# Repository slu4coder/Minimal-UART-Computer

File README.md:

# Minimal UART Computer - older version with EEPROMs

Current version: https://github.com/slu4coder/Minimal-UART-CPU-FLASH-Edition

Hi there, I built my own Computer from scratch - using nothing but TTL chips, because, well, that's what I wanted to do, I guess! I wanted
a CPU that is easy to understand, fun to build and powerful enough to allow for programming educational stuff and little games on it.
Ah, and by the way - it should be as simple as possible - sort of the "Simplest Usable Personal Computer Ever". Well, in case you're
interested, this repo aims to provide you with everything you need to follow my one-and-a-half year journey down this rabbit hole. 

WHAT YOU GET HERE:

  ● Block diagram of the CPU and overview it's instruction set

  ● KiCAD project files with detailed schematics and PCB layout

  ● Gerber files ready to be submitted at any PCB manufacturer of your choice

  ● Bill of material

  ● Images in .bin format of both the ROM and the CPU's control microcode

  ● Source code of the minimal operating system MinOS and several demos and games

  ● Cross-assembler 'asm.exe' running on Windows in order to comfortably write, assemble and upload your own software

TECHNICAL SPECIFICATION:

  ● Comparable to Altair 8800 or Apple 1

  ● Clear(est?) and simple(st? – you judge!) design for fun and education

  ● 8-bit data bus, 16-bit address bus, Von-Neumann architecture

  ● 64 instructions (conditional branching, subroutines, stack and word ops)

  ● 1,8432MHz clock with 0.25Mips (Altair 8800: 0.29Mips, Apple 1: 0.43Mips)

  ● 24kB RAM / 8kB ROM (OS, memory monitor, disassembler, tools, games)

  ● UART interface (115.2kbps) for terminal display, keyboard input and file I/O

  ● 16 control signals, 2 registers A and B, ALU (arithmetic and logic unit) = simple adder, 3 flags (negative, carry and zero)

  ● Built from 74HCxx TTL logic on 120mm x 190mm PCB

I hope you find this information useful, educational or otherwise interesting. I'd love to hear about you build, so meet me on YouTube.

https://www.youtube.com/channel/UCXYQcMpUBT3aaQKfmAVJNow

Cheers,
Slu4

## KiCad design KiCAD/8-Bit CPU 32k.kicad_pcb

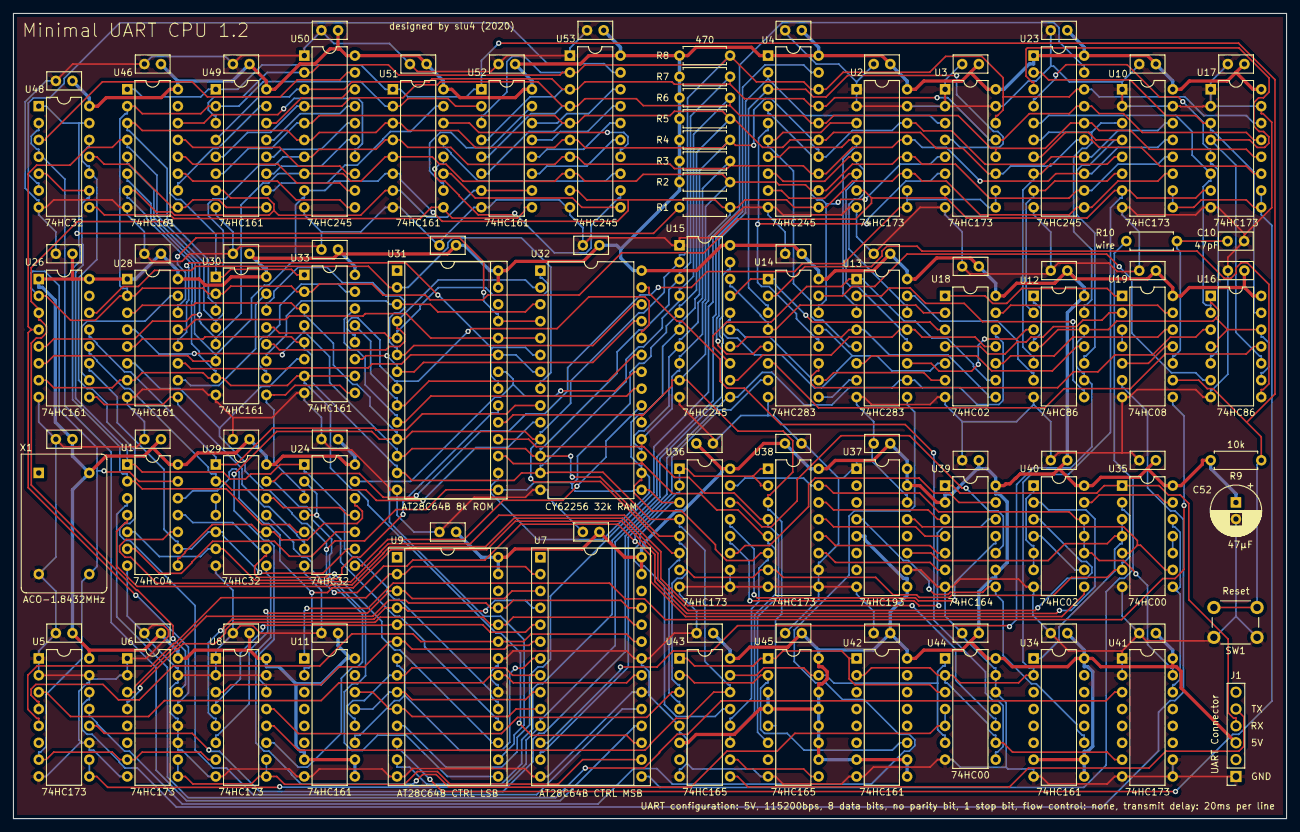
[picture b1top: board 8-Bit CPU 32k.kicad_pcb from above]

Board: 2 copper layers, 191.8 x 121.3 mm, 109 parts (0 on the bottom side), 166 nets.

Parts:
C1, C2, C3, C4, C5, C6, C7, C8, C9, C11, C12, C13, C14, C16, C17, C18, C19, C20, C21, C22, C23, C24, C25, C26, C27, C28, C29, C31, C32, C33, C34, C35, C36, C37, C39, C40, C41, C42, C43, C44, C45, C46, C47, C48, C49, C50, C51: 100nF; C_Disc_D5.0mm_W2.5mm_P2.50mm
C10: 47pF; C_Disc_D5.0mm_W2.5mm_P2.50mm
C52: 47µF; CP_Radial_D7.5mm_P2.50mm
J1: UART; PinSocket_1x06_P2.54mm_Vertical
R1, R2, R3, R4, R5, R6, R7, R8: 470; R_Axial_DIN0207_L6.3mm_D2.5mm_P7.62mm_Horizontal
R9: 10k; R_Axial_DIN0207_L6.3mm_D2.5mm_P7.62mm_Horizontal
R10: wire; R_Axial_DIN0207_L6.3mm_D2.5mm_P7.62mm_Horizontal
SW1: RESET; SW_PUSH_6mm
U1: 74HC04; DIP-14_W7.62mm
U2, U3, U5, U6, U8, U10, U17, U36, U38, U41: 74HC173; DIP-16_W7.62mm
U4, U15, U23, U50, U53: 74HC245; DIP-20_W7.62mm
U7: AT28C64B CTRL MSB; DIP-28_W15.24mm_Socket
U9: AT28C64B CTRL LSB; DIP-28_W15.24mm_Socket
U11, U26, U28, U30, U33, U34, U42, U46, U49, U51, U52: 74HC161; DIP-16_W7.62mm
U12, U16: 74HC86; DIP-14_W7.62mm
U13, U14: 74HC283; DIP-16_W7.62mm
U18, U40: 74HC02; DIP-14_W7.62mm
U19: 74HC08; DIP-14_W7.62mm
U24, U29, U48: 74HC32; DIP-14_W7.62mm
U31: AT28C64B 8k ROM; DIP-28_W15.24mm_Socket
U32: CY62256 32k RAM; DIP-28_W15.24mm
U35, U44: 74HC00; DIP-14_W7.62mm
U37: 74HC193; DIP-16_W7.62mm
U39: 74HC164; DIP-14_W7.62mm
U43, U45: 74HC165; DIP-16_W7.62mm
X1: ACO-1.8432MHz; Oscillator_DIP-14

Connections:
+5V: C1.1, C2.1, C3.1, C4.1, C5.1, C6.1, C7.1, C8.1, C9.1, C11.1, C12.1, C13.1, C14.1, C16.1, C17.1, C18.1, C19.1, C20.1, C21.1, C22.1, C23.1, C24.1, C25.1, C26.1, C27.1, C28.1, C29.1, C31.1, C32.1, C33.1, C34.1, C35.1, C36.1, C37.1, C39.1, C40.1, C41.1, C42.1, C43.1, C44.1, C45.1, C46.1, C47.1, C48.1, C49.1, C50.1, C51.1, C52.1, J1.3, R2.2, R3.2, R4.2, R5.2, R6.2, R7.2, R8.2, R9.2, U1.14, U2.16, U3.16, U4.1, U4.20, U5.16, U6.16, U7.27, U7.28, U8.16, U9.27, U9.28, U10.16, U11.7, U11.9, U11.10, U11.16, U12.14, U13.16, U14.16, U15.20, U16.14, U17.16, U18.14, U19.14, U23.1, U23.20, U24.14, U26.1, U26.16, U28.1, U28.16, U29.14, U30.16, U31.27, U31.28, U32.28, U33.16, U34.7, U34.9, U34.10, U34.16, U35.14, U36.16, U37.5, U37.9, U37.15, U37.16, U38.16, U39.2, U39.9, U39.14, U40.14, U41.16, U42.7, U42.9, U42.10, U42.16, U43.6, U43.16, U44.14, U45.3, U45.4, U45.10, U45.11, U45.12, U45.13, U45.14, U45.16, U46.16, U48.14, U49.16, U50.20, U51.16, U52.16, U53.20, X1.14
/ALU/A0: U3.3, U4.2, U14.5
/ALU/A1: U3.4, U4.3, U14.3
/ALU/A2: U3.5, U4.4, U14.14
/ALU/A3: U3.6, U4.5, U14.12
/ALU/A4: U2.3, U4.6, U13.5
/ALU/A5: U2.4, U4.7, U13.3
/ALU/A6: U2.5, U4.8, U13.14
/ALU/A7: U2.6, U4.9, U13.12
/ALU/B0: U16.13, U17.3, U23.2
/ALU/B1: U16.10, U17.4, U23.3
/ALU/B2: U16.5, U17.5, U23.4
/ALU/B3: U16.2, U17.6, U23.5
/ALU/B4: U10.3, U12.13, U23.6
/ALU/B5: U10.4, U12.10, U23.7
/ALU/B6: U10.5, U12.5, U23.8
/ALU/B7: U10.6, U12.2, U23.9
/ALU/BUS0: R8.1, U3.14, U4.18, U8.14, U15.2, U17.14, U23.18, U28.3, U31.11, U32.11, U33.3, U36.6, U43.4, U49.3, U50.2, U52.3, U53.2
/ALU/BUS1: R7.1, U3.13, U4.17, U8.13, U15.3, U17.13, U23.17, U28.4, U31.12, U32.12, U33.4, U36.5, U43.3, U49.4, U50.3, U52.4, U53.3
/ALU/BUS2: R6.1, U3.12, U4.16, U8.12, U15.4, U17.12, U23.16, U28.5, U31.13, U32.13, U33.5, U36.4, U43.14, U49.5, U50.4, U52.5, U53.4
/ALU/BUS3: R5.1, U3.11, U4.15, U8.11, U15.5, U17.11, U23.15, U28.6, U31.15, U32.15, U33.6, U36.3, U43.13, U49.6, U50.5, U52.6, U53.5
/ALU/BUS4: R4.1, U2.14, U4.14, U6.14, U10.14, U15.6, U23.14, U26.3, U30.3, U31.16, U32.16, U38.6, U43.12, U46.3, U50.6, U51.3, U53.6
/ALU/BUS5: R3.1, U2.13, U4.13, U6.13, U10.13, U15.7, U23.13, U26.4, U30.4, U31.17, U32.17, U38.5, U43.11, U46.4, U50.7, U51.4, U53.7
/ALU/BUS6: R2.1, U2.12, U4.12, U10.12, U15.8, U23.12, U26.5, U30.5, U31.18, U32.18, U38.4, U45.6, U46.5, U50.8, U51.5, U53.8
/ALU/BUS7: R1.2, U2.11, U4.11, U10.11, U15.9, U23.11, U26.6, U30.6, U31.19, U32.19, U38.3, U45.5, U46.6, U50.9, U51.6, U53.9
/ALU/EC: U7.13, U14.7
/ALU/ES: U7.12, U12.1, U12.4, U12.9, U12.12, U16.1, U16.4, U16.9, U16.12
/ALU/FLAG_C: U5.13, U13.9
/ALU/FLAG_N: U5.12, U13.10, U15.11, U18.12
/ALU/FLAG_Z: U5.14, U19.6
/ALU/~EO: U5.9, U5.10, U7.11, U15.19
/Control Logic/CE: U7.17, U26.7, U28.7, U30.7, U33.7, U33.10, U46.7, U49.7, U51.7, U52.7, U52.10
/Control Logic/HI: U1.1, U9.19, U24.1, U48.5, U48.9
/Control Logic/~AI: U2.9, U2.10, U3.9, U3.10, U9.15, U29.13
/Control Logic/~AO: U4.19, U9.13
/Control Logic/~BI: U9.12, U10.9, U10.10, U17.9, U17.10
/Control Logic/~BO: U9.11, U23.19
/Control Logic/~CI: U7.19, U48.10, U48.12
/Control Logic/~CO: U7.18, U48.2, U48.4
/Control Logic/~HI: R1.1, U1.2, U24.5, U48.1, U48.13
/Control Logic/~MI: U9.18, U24.2, U24.4
/Control Logic/~RI: U1.11, U9.17, U29.9
/Control Logic/~RO: U9.16, U24.13, U31.22, U32.22
/Memory/M0: U31.10, U32.21, U33.14
/Memory/M1: U31.9, U32.23, U33.13
/Memory/M2: U31.8, U32.24, U33.12
/Memory/M3: U31.7, U32.25, U33.11
/Memory/M4: U30.14, U31.6, U32.26
/Memory/M5: U30.13, U31.5, U32.1
/Memory/M6: U30.12, U31.4, U32.2
/Memory/M7: U30.11, U31.3, U32.3
/Memory/M8: U28.14, U31.25, U32.4
/Memory/M9: U28.13, U31.24, U32.5
/Memory/M10: U28.12, U31.21, U32.6
/Memory/M11: U28.11, U31.23, U32.7
/Memory/M12: U26.14, U31.2, U32.8
/Memory/M13: U26.13, U29.1, U32.9
/Memory/M14: U26.12, U29.2, U32.10
/Memory/M15: U1.9, U24.9, U26.11, U29.5
/Memory/~TI: U29.8, U44.4, U44.5
/Memory/~TO: U29.11, U36.1, U36.2, U38.1, U38.2, U40.8
/UART Receiver/RX: J1.4, U35.1, U39.1
/UART Receiver/~RESET: U35.5, U35.9, U37.13
/UART Transmitter/TX: J1.5, U43.9
CLOCK: U1.13, U2.7, U3.7, U5.7, U6.7, U8.7, U10.7, U17.7, U26.2, U28.2, U30.2, U33.2, U34.2, U41.7, U42.2, U44.2, U44.9, U46.2, U49.2, U51.2, U52.2, X1.8
GND: C1.2, C2.2, C3.2, C4.2, C5.2, C6.2, C7.2, C8.2, C9.2, C10.2, C11.2, C12.2, C13.2, C14.2, C16.2, C17.2, C18.2, C19.2, C20.2, C21.2, C22.2, C23.2, C24.2, C25.2, C26.2, C27.2, C28.2, C29.2, C31.2, C32.2, C33.2, C34.2, C35.2, C36.2, C37.2, C39.2, C40.2, C41.2, C42.2, C43.2, C44.2, C45.2, C46.2, C47.2, C48.2, C49.2, C50.2, C51.2, C52.2, J1.1, SW1.1, U1.7, U2.1, U2.2, U2.8, U2.15, U3.1, U3.2, U3.8, U3.15, U4.10, U5.1, U5.2, U5.8, U5.11, U5.15, U6.1, U6.2, U6.8, U6.11, U6.12, U6.15, U7.14, U7.20, U7.22, U8.1, U8.2, U8.8, U8.15, U9.14, U9.20, U9.22, U10.1, U10.2, U10.8, U10.15, U11.8, U12.7, U13.8, U14.8, U15.1, U15.10, U16.7, U17.1, U17.2, U17.8, U17.15, U18.7, U19.7, U23.10, U24.7, U26.8, U28.8, U29.7, U30.8, U31.14, U32.14, U33.8, U34.8, U35.7, U36.8, U36.9, U36.10, U37.1, U37.8, U37.10, U37.14, U38.8, U38.9, U38.10, U39.7, U40.7, U41.1, U41.2, U41.8, U41.9, U41.10, U42.8, U43.5, U43.8, U44.7, U44.12, U44.13, U45.8, U46.8, U48.7, U49.8, U50.1, U50.10, U51.8, U52.8, U53.1, U53.10, X1.7
unnamed: C10.1, R10.2, U19.10
unnamed: R10.1, U7.15
unnamed: U1.3, U41.3
unnamed: U1.4, U40.3
unnamed: U1.5, U29.6, U31.20
unnamed: U1.6, U24.10
unnamed: U1.8, U24.12, U29.10
unnamed: U1.10, U44.10
unnamed: U5.3, U7.21, U9.21
unnamed: U5.4, U7.23, U9.23
unnamed: U5.5, U7.2, U9.2
unnamed: U6.3, U7.25, U9.25
unnamed: U6.4, U7.24, U9.24
unnamed: U6.9, U6.10, U7.16, U8.9, U8.10
unnamed: U7.3, U8.6, U9.3
unnamed: U7.4, U8.5, U9.4
unnamed: U7.5, U8.4, U9.5
unnamed: U7.6, U8.3, U9.6
unnamed: U11.1, U19.8
unnamed: U7.7, U9.7, U11.11
unnamed: U7.8, U9.8, U11.12
unnamed: U7.9, U9.9, U11.13
unnamed: U7.10, U9.10, U11.14
unnamed: U12.3, U13.11
unnamed: U12.6, U13.15
unnamed: U12.8, U13.2
unnamed: U12.11, U13.6
unnamed: U13.1, U15.13, U18.9
unnamed: U13.4, U15.14, U18.8
unnamed: U13.7, U14.9
unnamed: U13.13, U15.12, U18.11
unnamed: U14.1, U15.17, U18.3
unnamed: U14.2, U16.8
unnamed: U14.4, U15.18, U18.2
unnamed: U14.6, U16.11
unnamed: U14.10, U15.15, U18.6
unnamed: U14.11, U16.3
unnamed: U14.13, U15.16, U18.5
unnamed: U14.15, U16.6
unnamed: U18.1, U19.1
unnamed: U18.4, U19.2
unnamed: U18.10, U19.12
unnamed: U18.13, U19.13
unnamed: U19.3, U19.4
unnamed: U19.5, U19.11
unnamed: U24.3, U30.9, U33.9
unnamed: U24.6, U26.9, U28.9
unnamed: U24.8, U32.20
unnamed: U24.11, U29.12
unnamed: U26.10, U28.15
unnamed: U28.10, U30.15
unnamed: U29.3, U29.4
unnamed: U30.10, U33.15
unnamed: U32.27, U44.8
unnamed: U34.1, U35.3, U35.4, U37.11
unnamed: U34.11, U37.4, U39.8
unnamed: U35.2, U35.6, U36.7, U38.7
unnamed: U35.10, U35.11
unnamed: U35.8, U35.12, U41.14
unnamed: U35.13, U40.13
unnamed: U36.11, U39.13
unnamed: U36.12, U39.12
unnamed: U36.13, U39.11
unnamed: U36.14, U39.10
unnamed: U36.15, U38.15, U40.10, U40.11, U40.12, U41.15
unnamed: U38.11, U39.6
unnamed: U38.12, U39.5
unnamed: U38.13, U39.4
unnamed: U38.14, U39.3
unnamed: U40.1, U40.5, U40.6
unnamed: U40.4, U40.9
unnamed: U42.1, U43.1, U44.3, U45.1
unnamed: U42.11, U43.2, U45.2
unnamed: U43.10, U45.9
unnamed: U43.15, U44.1, U44.6, U45.15
unnamed: U46.9, U48.11, U49.9
unnamed: U46.10, U49.15
unnamed: U46.11, U50.11
unnamed: U46.12, U50.12
unnamed: U46.13, U50.13
unnamed: U46.14, U50.14
unnamed: U48.3, U50.19
unnamed: U48.6, U53.19
unnamed: U48.8, U51.9, U52.9
unnamed: U49.10, U51.15
unnamed: U49.11, U50.15
unnamed: U49.12, U50.16
unnamed: U49.13, U50.17
unnamed: U49.14, U50.18
unnamed: U51.10, U52.15
unnamed: U51.11, U53.11
unnamed: U51.12, U53.12
unnamed: U51.13, U53.13
unnamed: U51.14, U53.14
unnamed: U52.11, U53.15
unnamed: U52.12, U53.16
unnamed: U52.13, U53.17
unnamed: U52.14, U53.18
~CLOCK: U1.12, U11.2, U40.2
~Reset: R9.1, SW1.2, U19.9, U30.1, U33.1, U46.1, U49.1, U51.1, U52.1

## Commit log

2020-12-14 Revision 1.2
2020-12-21 Version 1.2
2020-12-23 Revision 1.2.0
2021-02-12 Revision 1.3
    Abandoned the unnecessary instruction CLE for INP. On this architecture the following instructions are equivalent:
    INP = LDA $8000-$ffff and OUT = STA $8000-$ffff
    Now this instruction set is identical to that of the 'FLASH Edition' (but NOT the microcode).
    Have fun!
    slu4
2021-02-12 Revision 1.3
2021-02-12 Revision 1.3
    Calculator is now capable of parsing arbitrary math expressions.
